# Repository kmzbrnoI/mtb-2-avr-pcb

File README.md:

MTB-2-AVR PCB
=============

MTB-2-AVR is an expand module for old [MTB-UNI v2
PCBs](https://mtb.kmz-brno.cz/uni), [MTB-TTL/m v1](https://mtb.kmz-brno.cz/ttl)
modules and [MTB-UNIm v2 modules](https://mtb.kmz-brno.cz/unim). Its aim is to
replace old AT89C2051 CPU originally used these modules with a new ATmega8-like
processor. Purpose of the replacement is to allow old modules to communicate
over new bus protocol [TODO link].

Replacement: please remove old AT89C2051 CPU and place this board directly to
its DIL socket.

## Design

Schematics & PCB are designed in Eagle 9.

## Production

PCB is prepared to be automatically assembled in [JLCPCB](https://jlcpcb.com/).
SMD parts on top side should be assembled. Each SMD part has its `LCSC_ITEM`
attribute set.

1.0 mm or thinner PCB is advised.

## Deployment

To deploy to old MTB modules:

 * Check that RS485 driver has between pins 2 & 8 resistor of maximum value
   10k.
   - If not, either change resistor to 4k7 or remove RS485 transistor totally
     and remove resistor too.
   - Removing the transistor is slightly better as it will not cause RS485
     TX enable on boot. You can also add pull-down (~10k) to driver's DIR pin
     directly on PCB so when CPU board is removed DIR pin is in defined state.
 * Remove DS1706L IC.

## Authors

The module is designed by Jan Horáček,
[Model Railway Club Brno](https://www.kmz-brno.cz/).

## References

 * [MTB project](https://mtb.kmz-brno.cz) (in Czech)
 * MTBbus protocol [TODO]

## License

Content of the repository is provided under [Creative Commons
Attribution-ShareAlike 4.0
License](https://creativecommons.org/licenses/by-sa/4.0/) as openhardware
project. You may download any data, contribute to the project, create PCB
yourself or even sell it yourself.

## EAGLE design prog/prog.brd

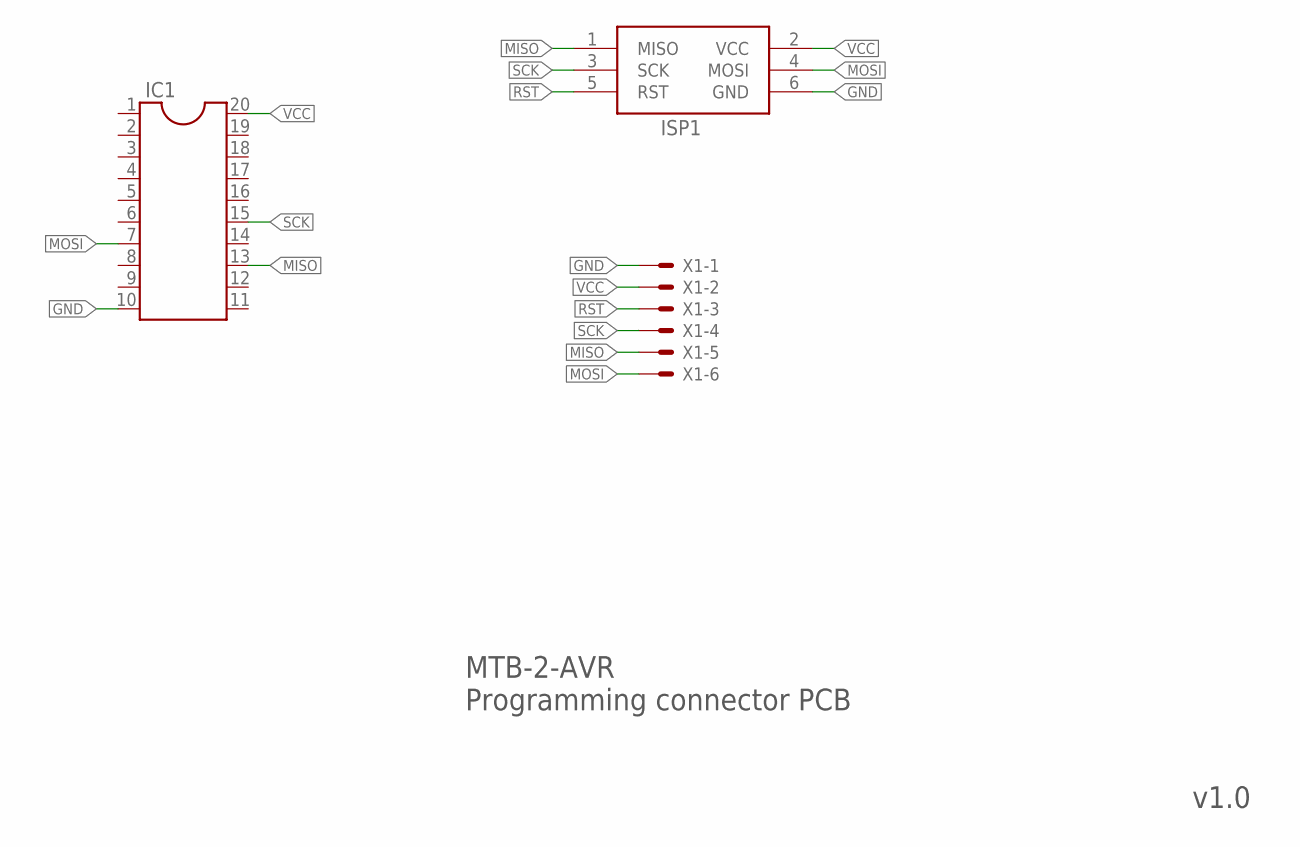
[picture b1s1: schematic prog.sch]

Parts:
IC1: DIL20
ISP1: AVRISP-6; AVRISP
X1: 22-23-2061

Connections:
GND: IC1.10, ISP1.6 (GND), X1.1
MISO: IC1.13, ISP1.1 (MISO), X1.5
MOSI: IC1.7, ISP1.4 (MOSI), X1.6
RST: ISP1.5 (RST), X1.3
SCK: IC1.15, ISP1.3 (SCK), X1.4
VCC: IC1.20, ISP1.2 (VCC), X1.2

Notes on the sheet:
MTB-2-AVR Programming connector PCB
v1.0

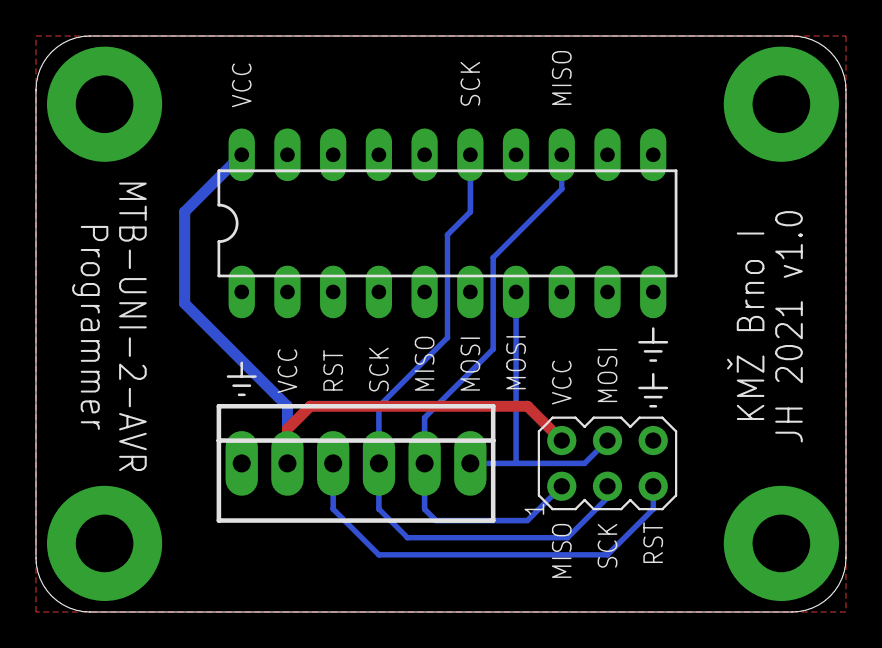
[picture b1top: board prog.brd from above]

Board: 2 copper layers, 45.0 x 32.0 mm, 3 parts (0 on the bottom side), 6 nets.

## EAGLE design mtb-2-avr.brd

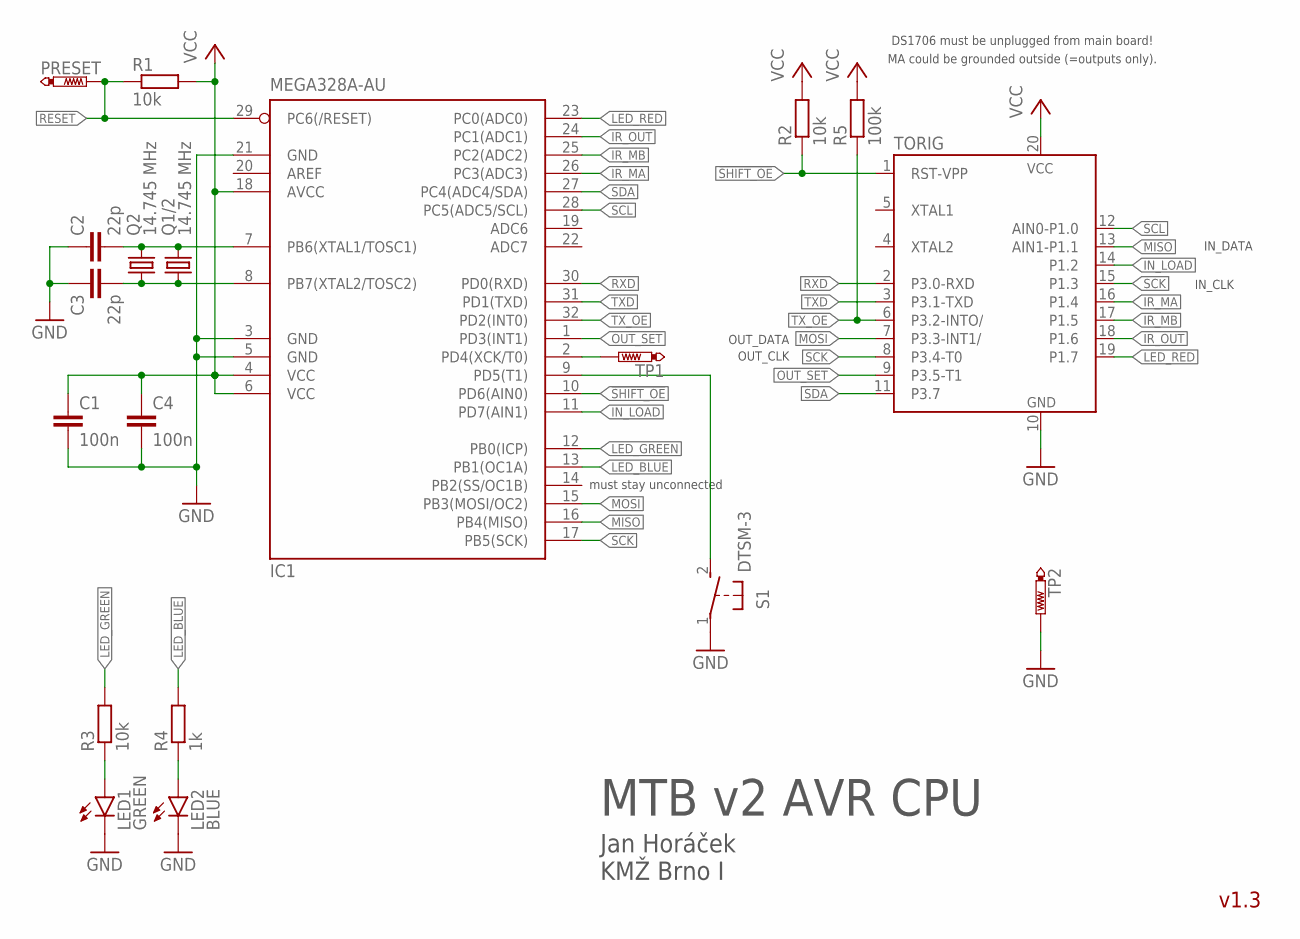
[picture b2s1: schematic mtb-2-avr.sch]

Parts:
C1, C4: 100n; C0603; LCSC_PART C14663
C2, C3: 22p; C0603; LCSC_PART C1653
IC1: MEGA328A-AU; TQFP32-08; LCSC_PART C14877
LED1: GREEN; CHIPLED_0603; LCSC_PART C72043
LED2: BLUE; CHIPLED_0603; LCSC_PART C72041
PRESET: PTR1B1,27; B1,27
Q1/2: 14.745 MHz; HC49UP; LCSC_PART C19646
Q2: 14.745 MHz; HC49/S
R1, R2, R3: 10k; R0603; LCSC_PART C25804
R4: 1k; R0603; LCSC_PART C21190
R5: 100k; R0603; LCSC_PART C25803
S1: DTSM-3
TORIG: AT89C2051; DIL20
TP1, TP2: PTR1B1,27; B1,27

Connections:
!SHIFT_OE: IC1.10 (PD6(AIN0)), R2.1, TORIG.1 (RST-VPP)
BTN: IC1.9 (PD5(T1)), S1.2
CRYST+: C2.2, IC1.7 (PB6(XTAL1/TOSC1)), Q1/2.2, Q2.2
CRYST-: C3.2, IC1.8 (PB7(XTAL2/TOSC2)), Q1/2.1, Q2.1
GND: C1.2, C2.1, C3.1, C4.2, IC1.3 (GND), IC1.5 (GND), IC1.21 (GND), LED1.C, LED2.C, S1.1, TORIG.10 (GND), TP2.TP
IN_LOAD: IC1.11 (PD7(AIN1)), TORIG.14 (P1.2)
IR_MA: IC1.26 (PC3(ADC3)), TORIG.16 (P1.4)
IR_MB: IC1.25 (PC2(ADC2)), TORIG.17 (P1.5)
IR_OUT: IC1.24 (PC1(ADC1)), TORIG.18 (P1.6)
LED_BLUE: IC1.13 (PB1(OC1A)), R4.2
LED_GREEN: IC1.12 (PB0(ICP)), R3.2
LED_RED: IC1.23 (PC0(ADC0)), TORIG.19 (P1.7)
MISO: IC1.16 (PB4(MISO)), TORIG.13 (AIN1-P1.1)
MOSI: IC1.15 (PB3(MOSI/OC2)), TORIG.7 (P3.3-INT1/)
unnamed: LED1.A, R3.1
unnamed: LED2.A, R4.1
OUT_SET: IC1.1 (PD3(INT1)), TORIG.9 (P3.5-T1)
RESET: IC1.29 (PC6(/RESET)), PRESET.TP, R1.1
RXD: IC1.30 (PD0(RXD)), TORIG.2 (P3.0-RXD)
SCK: IC1.17 (PB5(SCK)), TORIG.8 (P3.4-T0), TORIG.15 (P1.3)
SCL: IC1.28 (PC5(ADC5/SCL)), TORIG.12 (AIN0-P1.0)
SDA: IC1.27 (PC4(ADC4/SDA)), TORIG.11 (P3.7)
TEST1: IC1.2 (PD4(XCK/T0)), TP1.TP
TXD: IC1.31 (PD1(TXD)), TORIG.3 (P3.1-TXD)
TX_OE: IC1.32 (PD2(INT0)), R5.1, TORIG.6 (P3.2-INTO/)
VCC: C1.1, C4.1, IC1.4 (VCC), IC1.6 (VCC), IC1.18 (AVCC), R1.2, R2.2, R5.2, TORIG.20 (VCC)

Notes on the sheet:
MTB v2 AVR CPU
Jan Horáček KMŽ Brno I
v1.3
DS1706 must be unplugged from main board!
MA could be grounded outside (=outputs only).
OUT_DATA
OUT_CLK
IN_CLK
IN_DATA
must stay unconnected

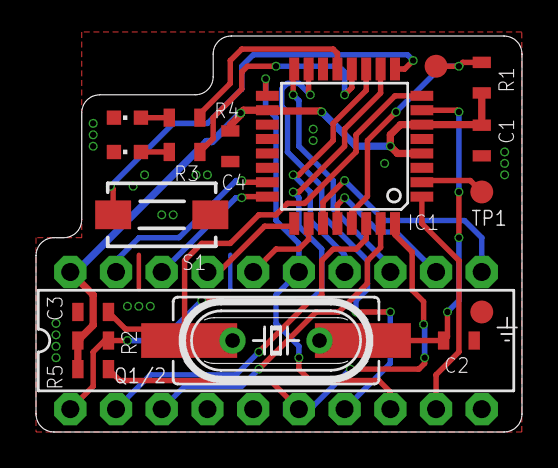
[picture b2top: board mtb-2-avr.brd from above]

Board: 2 copper layers, 27.0 x 22.0 mm, 19 parts (0 on the bottom side), 26 nets.

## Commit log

2020-12-04 Add .gitignore.
2020-12-04 Add README.
2020-12-04 Add schematics & library.
2020-12-04 Add wires to schematics, create pcb template.
2021-02-12 Sch: connect must-signals.
2021-02-12 Connect all wires.
2021-02-12 Route everything.
2021-02-12 Round corners.
2021-02-12 Add texts.
2021-02-13 Use 0603 SMDs with smaller clearance.
2021-02-13 Add LCSC parts numbers.
2021-02-13 Minor fixes.
2021-02-15 Add readme & license
2021-02-20 Add button, rewire, remove prog. connector.
2021-02-22 Use ATmega8A, fix silksreen.
2021-02-22 Silkscreen tweaks.
2021-03-02 Add test pad.
2021-03-02 Add GND testpads.
2021-03-02 Add possibility for THT crystal.
2021-03-04 Make ground plane larger, add GND vias.
2021-03-25 Free PB2, connect SHIFT_OE.
    PB2 must be free because SPI uses it. Disconnected SHIFT_OE was bug.
2021-03-25 CPU socket: drills 0.8 mm → 1.0 mm
2021-03-25 Minor silkcreen tweak.
2021-03-25 Cover via in soldermask.
2021-03-26 Add pull-up on TX_OE.
2021-03-30 Minor tweaks of wire positions.
2021-04-13 Use ATmega328.
2021-04-21 Change outer dimensions to fit to MTB-TTL.
2021-05-02 Add programming PCB.
2021-05-10 README: add note about deployment.
2021-05-10 README: add note about embedded pull-down.
